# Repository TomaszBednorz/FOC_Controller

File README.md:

# FOC_Controller - in progress

## Description

The main goal of this project is to design a driver for a PMSM (Permanent Magnet Synchronous Motor) and implement the FOC (Field-Oriented Control) algorithm in software - in the future.

## Hardware overview

More information: [Hardware folder](https://github.com/TomaszBednorz/FOC_Controller/tree/main/HW)

## Figres

The FOC controller and PMSM motor.  

## STM32CubeIDE template

Empty project with pins and peripherals configuration: [Template](https://github.com/TomaszBednorz/FOC_Controller/tree/main/Tools/STM32CubeIDE_projects/STM32G473RC_template)

## Software overview

TBD

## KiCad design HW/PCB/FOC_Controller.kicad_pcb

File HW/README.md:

# FOC_Controller – Hardware

## Description

This folder contains:
- Source files of the PCB design in KiCad: [PCB folder](https://github.com/TomaszBednorz/FOC_Controller/tree/main/HW/PCB)
- STL files for the motor driver enclosure.

## 3D Visualization

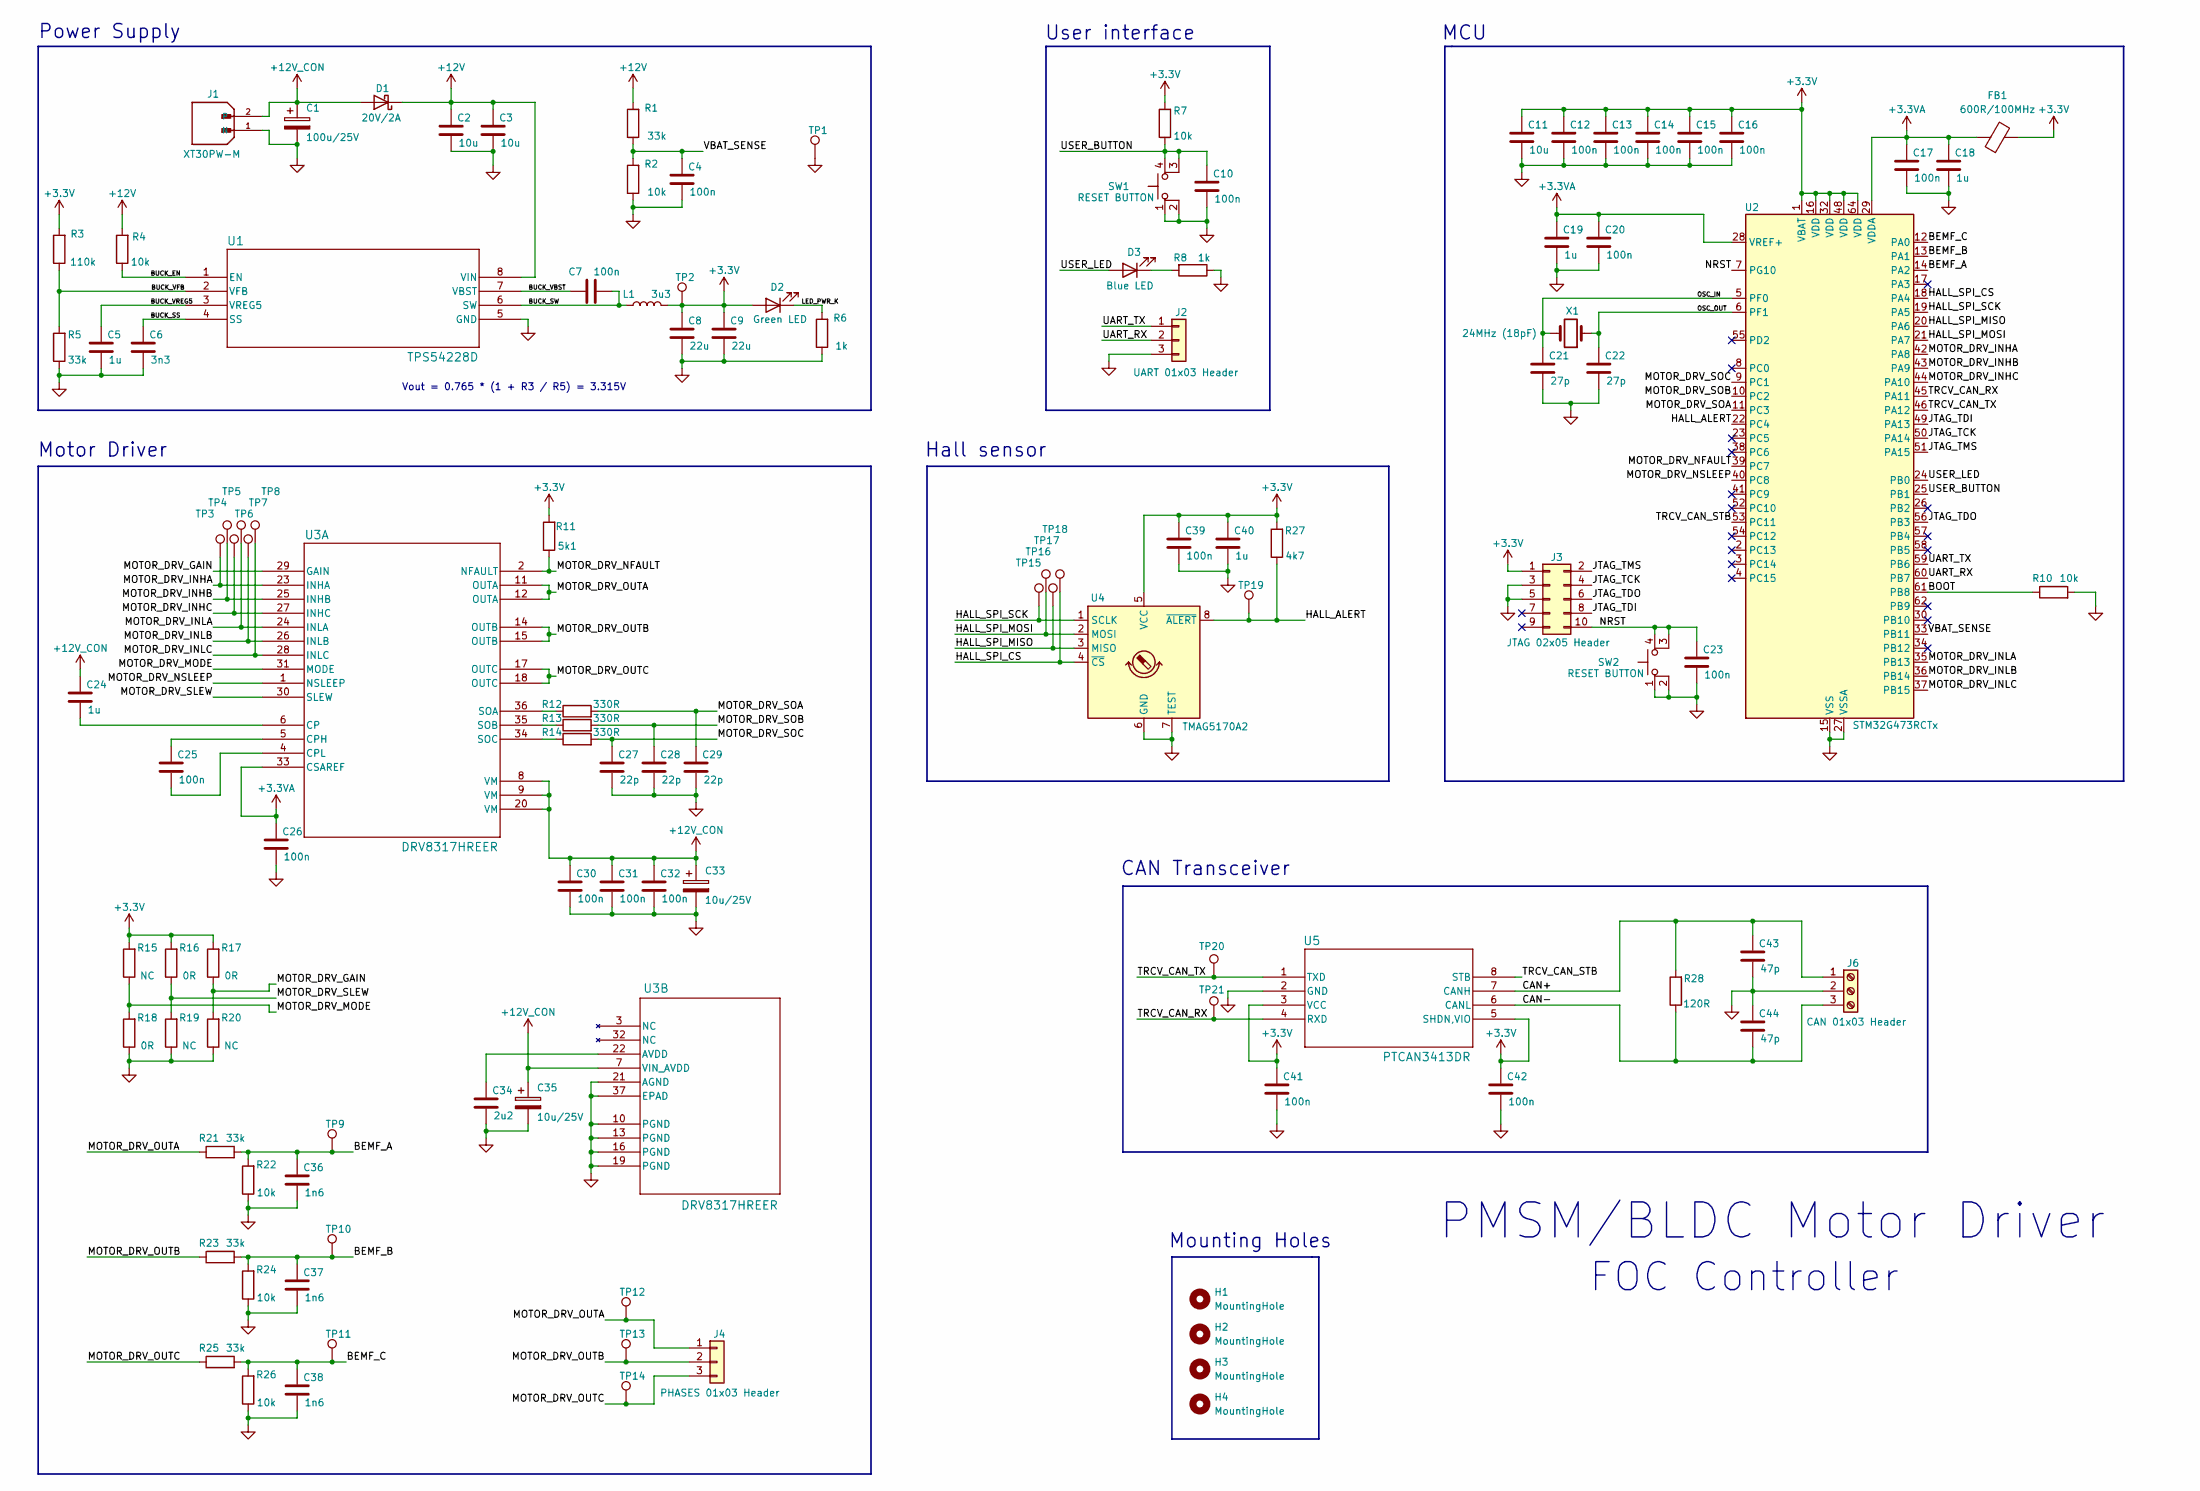
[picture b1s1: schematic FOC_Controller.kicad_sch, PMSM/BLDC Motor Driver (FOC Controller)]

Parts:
C1: 100u/25V; CP_Radial_D6.3mm_P2.50mm
C2, C3, C11: 10u; C_0805_2012Metric_Pad1.18x1.45mm_HandSolder
C4, C7, C10, C12, C13, C14, C15, C16, C17, C20, C23, C25, C26, C30, C31, C32, C39, C41, C42: 100n; C_0805_2012Metric_Pad1.18x1.45mm_HandSolder
C5, C18, C19, C24, C40: 1u; C_0805_2012Metric_Pad1.18x1.45mm_HandSolder
C6: 3n3; C_0805_2012Metric_Pad1.18x1.45mm_HandSolder
C8, C9: 22u; C_0805_2012Metric_Pad1.18x1.45mm_HandSolder
C21, C22: 27p; C_0603_1608Metric_Pad1.08x0.95mm_HandSolder
C27, C28, C29: 22p; C_0805_2012Metric_Pad1.18x1.45mm_HandSolder
C33, C35: 10u/25V; CP_Elec_4x3.9
C34: 2u2; C_0805_2012Metric_Pad1.18x1.45mm_HandSolder
C36, C37, C38: 1n6; C_0603_1608Metric_Pad1.08x0.95mm_HandSolder
C43, C44: 47p; C_0603_1608Metric_Pad1.08x0.95mm_HandSolder
D1: 20V/2A; D_SMB
D2: Green LED; LED_0805_2012Metric_Pad1.15x1.40mm_HandSolder
D3: Blue LED; LED_0805_2012Metric_Pad1.15x1.40mm_HandSolder
FB1: 600R/100MHz; L_0805_2012Metric_Pad1.05x1.20mm_HandSolder
H1, H2, H3, H4: MountingHole; MountingHole_2.2mm_M2
J1: XT30PW-M; AMASS_XT30PW-M_1x02_P2.50mm_Horizontal; PARTREV 1.2
J2: UART 01x03 Header; PinHeader_1x03_P2.54mm_Vertical
J3: JTAG 02x05 Header; PinHeader_2x05_P1.27mm_Vertical_SMD
J4: PHASES 01x03 Header; PinHeader_1x03_P2.54mm_Vertical
J6: CAN 01x03 Header; TerminalBlock_MetzConnect_Type059_RT06303HBWC_1x03_P3.50mm_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
L1: 3u3; L_APV_ANR4012
R1, R5, R21, R23, R25: 33k; R_0805_2012Metric_Pad1.20x1.40mm_HandSolder
R2, R4, R7, R10, R22, R24, R26: 10k; R_0805_2012Metric_Pad1.20x1.40mm_HandSolder
R3: 110k; R_0805_2012Metric_Pad1.20x1.40mm_HandSolder
R6, R8: 1k; R_0805_2012Metric_Pad1.20x1.40mm_HandSolder
R11: 5k1; R_0805_2012Metric_Pad1.20x1.40mm_HandSolder
R12, R13, R14: 330R; R_0805_2012Metric_Pad1.20x1.40mm_HandSolder
R15, R19, R20: NC; R_0805_2012Metric_Pad1.20x1.40mm_HandSolder
R16, R17, R18: 0R; R_0805_2012Metric_Pad1.20x1.40mm_HandSolder
R27: 4k7; R_0805_2012Metric_Pad1.20x1.40mm_HandSolder
R28: 120R; R_0805_2012Metric_Pad1.20x1.40mm_HandSolder
SW1, SW2: RESET BUTTON; SW_TS04-66-55-BK-100-SMT-TR
TP1, TP2, TP3, TP4, TP5, TP6, TP7, TP8, TP9, TP10, TP11, TP12, TP13, TP14, TP15, TP16, TP17, TP18, TP19, TP20, TP21: TestPoint; TestPoint_Pad_D1.0mm
U1: TPS54228D; SOIC-8_3.9x4.9mm_P1.27mm
U2: STM32G473RCTx; LQFP-64_10x10mm_P0.5mm
U3: DRV8317HREER; WQFN36_REE_TEX-L
U4: TMAG5170A2; VSSOP-8_3x3mm_P0.65mm
U5: PTCAN3413DR; SOIC-8_3.9x4.9mm_P1.27mm
X1: 24MHz (18pF); Crystal_SMD_Abracon_ABM3-2Pin_5.0x3.2mm_HandSoldering

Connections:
+3.3V: C8.1, C9.1, C11.1, C12.1, C13.1, C14.1, C15.1, C16.1, C39.1, C40.1, C41.1, C42.1, D2.2 (A), FB1.2, J3.1, L1.2, R3.2, R7.2, R11.2, R15.2, R16.2, R17.2, R27.2, TP2.1, U2.1 (VBAT), U2.16 (VDD), U2.32 (VDD), U2.48 (VDD), U2.64 (VDD), U4.5 (VCC), U5.3 (VCC), U5.5 (SHDN,VIO)
+3.3VA: C17.1, C18.1, C19.1, C20.1, C26.1, FB1.1, U2.28 (VREF+), U2.29 (VDDA), U3.33 (CSAREF)
+12V: C2.1, C3.1, D1.1 (K), R1.2, R4.2, U1.8 (VIN)
+12V_CON: C1.1, C24.1, C30.1, C31.1, C32.1, C33.1, C35.1, D1.2 (A), J1.2, U3.7 (VIN_AVDD), U3.8 (VM), U3.9 (VM), U3.20 (VM)
/BEMF_A: C36.1, R21.2, R22.2, TP9.1, U2.14 (PA2)
/BEMF_B: C37.1, R23.2, R24.2, TP10.1, U2.13 (PA1)
/BEMF_C: C38.1, R25.2, R26.2, TP11.1, U2.12 (PA0)
/BOOT: R10.1, U2.61 (PB8)
/BUCK_EN: R4.1, U1.1 (EN)
/BUCK_SS: C6.1, U1.4 (SS)
/BUCK_SW: C7.2, L1.1, U1.6 (SW)
/BUCK_VBST: C7.1, U1.7 (VBST)
/BUCK_VFB: R3.1, R5.2, U1.2 (VFB)
/BUCK_VREG5: C5.1, U1.3 (VREG5)
/CAN+: C43.1, J6.1, R28.2, U5.7 (CANH)
/CAN-: C44.2, J6.3, R28.1, U5.6 (CANL)
/HALL_ALERT: R27.1, TP19.1, U2.22 (PC4), U4.8 (~ALERT)
/HALL_SPI_CS: TP18.1, U2.18 (PA4), U4.4 (~CS)
/HALL_SPI_MISO: TP17.1, U2.20 (PA6), U4.3 (MISO)
/HALL_SPI_MOSI: TP16.1, U2.21 (PA7), U4.2 (MOSI)
/HALL_SPI_SCK: TP15.1, U2.19 (PA5), U4.1 (SCLK)
/JTAG_TCK: J3.4, U2.50 (PA14)
/JTAG_TDI: J3.8, U2.49 (PA13)
/JTAG_TDO: J3.6, U2.56 (PB3)
/JTAG_TMS: J3.2, U2.51 (PA15)
/LED_PWR_K: D2.1 (K), R6.2
/MOTOR_DRV_GAIN: R17.1, R20.2, U3.29 (GAIN)
/MOTOR_DRV_INHA: TP3.1, U2.42 (PA8), U3.23 (INHA)
/MOTOR_DRV_INHB: TP4.1, U2.43 (PA9), U3.25 (INHB)
/MOTOR_DRV_INHC: TP5.1, U2.44 (PA10), U3.27 (INHC)
/MOTOR_DRV_INLA: TP6.1, U2.35 (PB13), U3.24 (INLA)
/MOTOR_DRV_INLB: TP7.1, U2.36 (PB14), U3.26 (INLB)
/MOTOR_DRV_INLC: TP8.1, U2.37 (PB15), U3.28 (INLC)
/MOTOR_DRV_MODE: R15.1, R18.2, U3.31 (MODE)
/MOTOR_DRV_NFAULT: R11.1, U2.39 (PC7), U3.2 (NFAULT)
/MOTOR_DRV_NSLEEP: U2.40 (PC8), U3.1 (NSLEEP)
/MOTOR_DRV_OUTA: J4.1, R21.1, TP12.1, U3.11 (OUTA), U3.12 (OUTA)
/MOTOR_DRV_OUTB: J4.2, R23.1, TP13.1, U3.14 (OUTB), U3.15 (OUTB)
/MOTOR_DRV_OUTC: J4.3, R25.1, TP14.1, U3.17 (OUTC), U3.18 (OUTC)
/MOTOR_DRV_SLEW: R16.1, R19.2, U3.30 (SLEW)
/MOTOR_DRV_SOA: C29.1, R12.2, U2.11 (PC3)
/MOTOR_DRV_SOB: C28.1, R13.2, U2.10 (PC2)
/MOTOR_DRV_SOC: C27.1, R14.2, U2.9 (PC1)
/NRST: C23.1, J3.10, SW2.3 (K), SW2.4 (A), U2.7 (PG10)
/OSC_IN: C21.1, U2.5 (PF0), X1.2
/OSC_OUT: C22.1, U2.6 (PF1), X1.1
/TRCV_CAN_RX: TP21.1, U2.45 (PA11), U5.4 (RXD)
/TRCV_CAN_STB: U2.53 (PC11), U5.8 (STB)
/TRCV_CAN_TX: TP20.1, U2.46 (PA12), U5.1 (TXD)
/UART_RX: J2.2, U2.60 (PB7)
/UART_TX: J2.1, U2.59 (PB6)
/USER_BUTTON: C10.1, R7.1, SW1.3 (K), SW1.4 (A), U2.25 (PB1)
/USER_LED: D3.2 (A), U2.24 (PB0)
/VBAT_SENSE: C4.1, R1.1, R2.2, U2.33 (PB11)
GND: C1.2, C2.2, C3.2, C4.2, C5.2, C6.2, C8.2, C9.2, C10.2, C11.2, C12.2, C13.2, C14.2, C15.2, C16.2, C17.2, C18.2, C19.2, C20.2, C21.2, C22.2, C23.2, C26.2, C27.2, C28.2, C29.2, C30.2, C31.2, C32.2, C33.2, C34.2, C35.2, C36.2, C37.2, C38.2, C39.2, C40.2, C41.2, C42.2, C43.2, C44.1, J1.1 (N), J2.3, J3.3, J3.5, J6.2, R2.1, R5.1, R6.1, R8.1, R10.2, R18.1, R19.1, R20.1, R22.1, R24.1, R26.1, SW1.1, SW1.2, SW2.1, SW2.2, TP1.1, U1.5 (GND), U2.15 (VSS), U2.27 (VSSA), U2.31 (VSS), U2.47 (VSS), U2.63 (VSS), U3.10 (PGND), U3.13 (PGND), U3.16 (PGND), U3.19 (PGND), U3.21 (AGND), U3.37 (EPAD), U4.6 (GND), U4.7 (TEST), U5.2 (GND)
unnamed: D3.1 (K), R8.2
unnamed: C24.2, U3.6 (CP)
unnamed: C25.1, U3.5 (CPH)
unnamed: C25.2, U3.4 (CPL)
unnamed: R12.1, U3.36 (SOA)
unnamed: R13.1, U3.35 (SOB)
unnamed: R14.1, U3.34 (SOC)
unnamed: C34.1, U3.22 (AVDD)

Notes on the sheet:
Power Supply
User interface
Mounting Holes
Hall sensor
CAN Transceiver
MCU
Motor Driver
Vout = 0.765 * (1 + R3 / R5) = 3.315V
PMSM/BLDC Motor Driver
FOC Controller

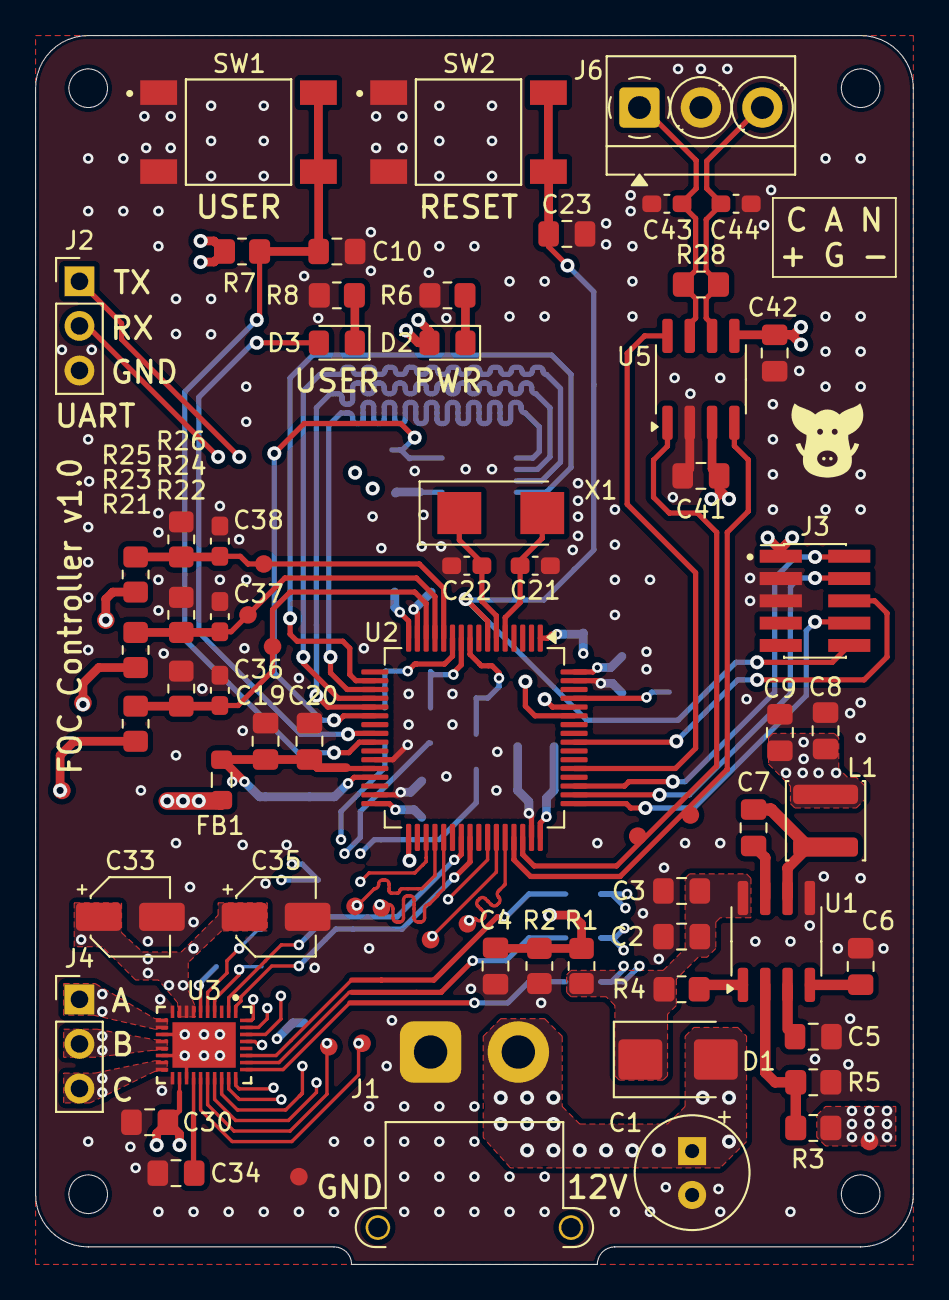
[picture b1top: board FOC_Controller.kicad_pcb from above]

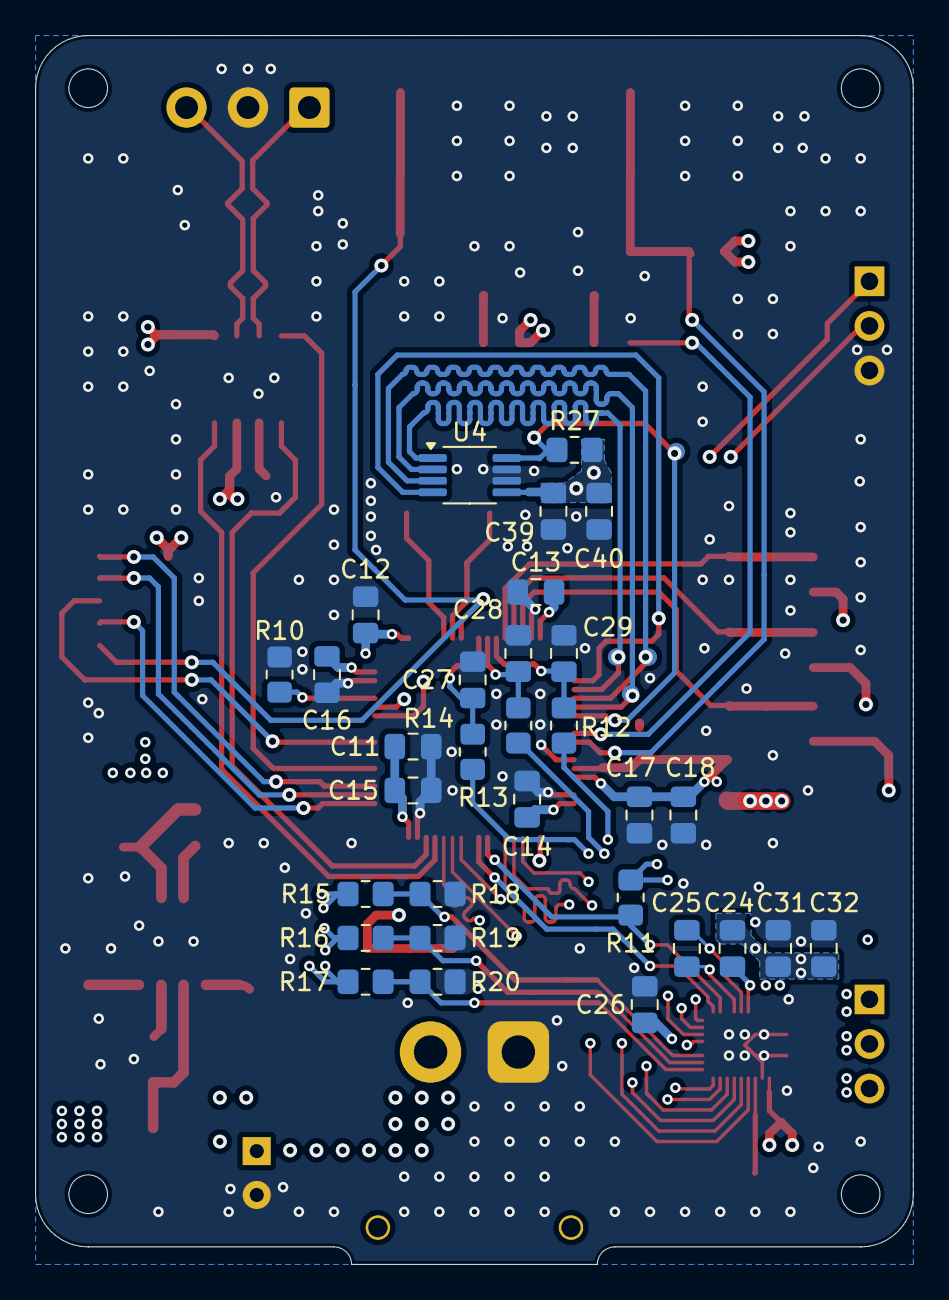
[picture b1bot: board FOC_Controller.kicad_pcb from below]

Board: 4 copper layers, 50.0 x 70.0 mm, 114 parts (36 on the bottom side), 63 nets.

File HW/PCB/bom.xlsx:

Component | Name | Price [zl] | Quantity | Sum | Status | Code case | Link | Designator
Integrated circuits
MCU | STM32G473RCT6 | 20.94 | 2 | 41.88 | Mouser |  | https://www.mouser.pl/ProductDetail/STMicroelectronics/STM32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 | U2
Motor driver | DRV8317HREER | 9.2899999999999991 | 2 | 18.579999999999998 | Mouser |  | https://www.mouser.pl/ProductDetail/Texas-Instruments/DRV831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 | U3
CAN-FD transceiver | TCAN3414DR | 5.81 | 2 | 11.62 | Mouser |  | https://www.mouser.pl/ProductDetail/Texas-Instruments/TCAN34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 | U5
Hall sensor | TMAG5170A2QDGKR | 7.1 | 2 | 14.2 | Mouser |  | https://www.mouser.pl/ProductDetail/Texas-Instruments/TMAG51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 | U4
Step-down converter | TPS54228D | 4.6900000000000004 | 2 | 9.3800000000000008 | Mouser |  | https://www.mouser.pl/ProductDetail/Texas-Instruments/TPS542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 | U1
Resistors
33k | CRCW080533K0FKEBC | 6.5000000000000002E-2 | 15 | 0.97500000000000009 | Mouser | 0805 | https://www.mouser.pl/ProductDetail/Vishay-Dale/CRCW080533K0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 | R1, R5, R21, R23, R25
10k | CRCW080510K0FKEA | 0.17199999999999999 | 21 | 3.6119999999999997 | Mouser | 0805 | https://www.mouser.pl/ProductDetail/Vishay-Dale/CRCW080510K0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 | R2, R4, R7, R10, R22, R24, R26
110k | CRCW0805110KFKEAC | 9.9000000000000005E-2 | 10 | 0.99 | Mouser | 0805 | https://www.mouser.pl/ProductDetail/Vishay-Dale/CRCW0805110K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 | R3
1k | CRCW08051K00FKEAC | 9.9000000000000005E-2 | 10 | 0.99 | Mouser | 0805 | https://www.mouser.pl/ProductDetail/Vishay-Dale/CRCW08051K00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 | R6,R8
0R | AC0805FR-070RL | 6.5000000000000002E-2 | 10 | 0.65 | Mouser | 0805 | https://www.mouser.pl/ProductDetail/YAGEO/AC0805FR-070RL?qs=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 | R9 (brak), R16, R17, R19
5k1 | CRCW08055K10FKEAC | 9.9000000000000005E-2 | 10 | 0.99 | Mouser | 0805 | https://www.mouser.pl/ProductDetail/Vishay-Dale/CRCW08055K10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 | R11
330R | CRCW0805330RFKEA | 0.10299999999999999 | 10 | 1.03 | Mouser | 0805 | https://www.mouser.pl/ProductDetail/Vishay-Dale/CRCW0805330R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 | R12, R13, R14 |  |  |  |  |  |  |  |  |  |  |  |  |  |  | -
4k7 | CRCW08054K70FKEA | 0.12 | 10 | 1.2 | Mouser | 0805 | https://www.mouser.pl/ProductDetail/Vishay-Dale/CRCW08054K70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 | R27
120R | CRCW0805120RFKEA | 0.159 | 10 | 1.59 | Mouser | 0805 | https://www.mouser.pl/ProductDetail/Vishay-Dale/CRCW0805120R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 | R28
NC |  |  | 9 | 0 |  |  |  | R15, R19, R20
Capacitors
100u/25V, electrolytic | 860010473007 | 0.53 | 2 | 1.06 | Mouser | THT | https://www.mouser.pl/ProductDetail/Wurth-Elektronik/8600104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 | C1
10u/25V | CL21A106KAYNNNG | 0.30099999999999999 | 10 | 3.01 | Mouser | 0805 | https://www.mouser.pl/ProductDetail/Samsung-Electro-Mechanic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 | C2, C3, C11
100n/50V | CL21B104KBCNNND | 7.6999999999999999E-2 | 100 | 7.7 | Mouser | 0805 | https://www.mouser.pl/ProductDetail/Samsung-Electro-Mechanic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 | C4, C7, C10, C12, C13, C14, C15, C16, C17, C20, C23, C25, C26, C30, C31, C32, C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
1u/50V | CL21B105KBFNNNE | 0.151 | 15 | 2.2650000000000001 | Mouser | 0805 | https://www.mouser.pl/ProductDetail/Samsung-Electro-Mechanic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 | C5, C18, C19, C24, C40
3n3/25V | 885012207063 | 0.155 | 10 | 1.55 | Mouser | 0805 | https://www.mouser.pl/ProductDetail/Wurth-Elektronik/8850122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 | C6
22u/25V | CL21A226MAYNNNE | 0.42599999999999999 | 15 | 6.39 | Mouser | 0805 | https://www.mouser.pl/ProductDetail/Samsung-Electro-Mechanic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 | C8, C9, C27, C28, C29
27p/50V | CL10C270JB81PNC | 0.11600000000000001 | 10 | 1.1600000000000001 | Mouser | 0603 | https://www.mouser.pl/ProductDetail/Samsung-Electro-Mechanic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 | C21, C22
10u/25V, electrolytic | 865080440002 | 0.74 | 4 | 2.96 | Mouser | SMD | https://www.mouser.pl/ProductDetail/Wurth-Elektronik/8650804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 | C33, C35
2u2/25V | CL21A225KAFNNNG | 0.219 | 10 | 2.19 | Mouser | 0805 | https://www.mouser.pl/ProductDetail/Samsung-Electro-Mechanic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 | C34
1n6/50V | GRM1885C1H162JA01D | 0.129 | 10 | 1.29 | TME | 0603 | https://www.tme.eu/pl/details/grm1885c1h162ja01d/kondensator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 | C36, C37, C38
47p | CL10C470JC81PNC | 0.16300000000000001 | 10 | 1.6300000000000001 | Mouser | 0603 | https://www.mouser.pl/ProductDetail/Samsung-Electro-Mechanic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 | C43, C44
Inductors
3u3 | NRS4012T3R3MDGJ | 0.78 | 3 | 2.34 | Mouser |  | https://www.mouser.pl/ProductDetail/TAIYO-YUDEN/NRS4012T3R3M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 | L1
Diodes
Schottky Diodes | SK22 | 0.74 | 3 | 2.2199999999999998 | Mouser |  | https://www.mouser.pl/ProductDetail/Diotec-Semiconductor/SK2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 | D1
LED green | 150080GS75000 | 0.78 | 3 | 2.34 | Mouser |  | https://www.mouser.pl/ProductDetail/Wurth-Elektronik/150080G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 | D2
LED blue | 150080BS75000 | 0.78 | 3 | 2.34 | Mouser |  | https://www.mouser.pl/ProductDetail/Wurth-Elektronik/150080B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 | D3
Ferrite Beads
600R/100Mhz | MPZ2012S601ATD25 | 0.28000000000000003 | 10 | 2.8000000000000003 | Mouser | 0805 | https://www.mouser.pl/ProductDetail/TDK/MPZ2012S601ATD25?qs=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 | FB1
Cristals
24MHz | ABM3-24.000MHZ-D2Y-T | 2.21 | 2 | 4.42 | Mouser |  | https://www.mouser.pl/ProductDetail/ABRACON/ABM3-24.000MHZ-D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 | X1
Switches
Tactile Switch | TS04-66-55-BK-100-SMT | 0.66 | 4 | 2.64 | Mouser |  | https://www.mouser.pl/ProductDetail/Same-Sky/TS04-66-55-BK-1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 | SW1, SW2
Connectors
DC male connector | XT30PW-M | 2.54 | 2 | 5.08 | TME |  | https://www.tme.eu/pl/details/xt30pw-m/zlacza-dc/amass/ | J1
DC female connector | XT30U-F | 1.75 | 2 | 3.5 | TME |  | https://www.tme.eu/pl/details/xt30u-f/zlacza-dc/amass/ | J1
Header 1x10 (goldpin) | 10129378-910001BLF | 0.78 | 2 | 1.56 | Mouser |  | https://www.mouser.pl/ProductDetail/Amphenol-FCI/10129378-91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 | J2, J4
Header 2x5 | 20021121-00010T4LF | 3.23 | 2 | 6.46 | Mouser |  | https://www.mouser.pl/ProductDetail/Amphenol-FCI/20021121-00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 | J3
Screw terminal 1x3 | EBWA-03-A | 1.76 | 2 | 3.52 | Mouser |  | https://www.mouser.pl/ProductDetail/Adam-Tech/EBWA-03-A?qs=H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 | J6
Jumper 1x2 | MSA-G | 0.41 | 3 | 1.23 | Mouser |  | https://www.mouser.pl/ProductDetail/Adam-Tech/MSA-G?qs=TTVbH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 | J5
 |  |  | Łącznie | 179.34199999999998

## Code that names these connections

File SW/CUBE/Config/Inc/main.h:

/* USER CODE BEGIN Header */
/**
  ******************************************************************************
  * @file           : main.h
  * @brief          : Header for main.c file.
  *                   This file contains the common defines of the application.
  ******************************************************************************
  * @attention
  *
  * Copyright (c) 2025 STMicroelectronics.
  * All rights reserved.
  *
  * This software is licensed under terms that can be found in the LICENSE file
  * in the root directory of this software component.
  * If no LICENSE file comes with this software, it is provided AS-IS.
  *
  ******************************************************************************
  */
/* USER CODE END Header */

/* Define to prevent recursive inclusion -------------------------------------*/
#ifndef __MAIN_H
#define __MAIN_H

#ifdef __cplusplus
extern "C" {
#endif

/* Includes ------------------------------------------------------------------*/
#include "stm32g4xx_hal.h"

/* Private includes ----------------------------------------------------------*/
/* USER CODE BEGIN Includes */

/* USER CODE END Includes */

/* Exported types ------------------------------------------------------------*/
/* USER CODE BEGIN ET */

/* USER CODE END ET */

/* Exported constants --------------------------------------------------------*/
/* USER CODE BEGIN EC */

/* USER CODE END EC */

/* Exported macro ------------------------------------------------------------*/
/* USER CODE BEGIN EM */

/* USER CODE END EM */

/* Exported functions prototypes ---------------------------------------------*/
void Error_Handler(void);

/* USER CODE BEGIN EFP */

/* USER CODE END EFP */

/* Private defines -----------------------------------------------------------*/
#define DEBUG_PIN_RED_Pin GPIO_PIN_13
#define DEBUG_PIN_RED_GPIO_Port GPIOC
#define DEBUG_PIN_BLUE_Pin GPIO_PIN_15
#define DEBUG_PIN_BLUE_GPIO_Port GPIOC
#define NRST_Pin GPIO_PIN_10
#define NRST_GPIO_Port GPIOG
#define MOTOR_DRV_SOC_Pin GPIO_PIN_1
#define MOTOR_DRV_SOC_GPIO_Port GPIOC
#define MOTOR_DRV_SOB_Pin GPIO_PIN_2
#define MOTOR_DRV_SOB_GPIO_Port GPIOC
#define MOTOR_DRV_SOA_Pin GPIO_PIN_3
#define MOTOR_DRV_SOA_GPIO_Port GPIOC
#define BEMF_C_Pin GPIO_PIN_0
#define BEMF_C_GPIO_Port GPIOA
#define BEMF_B_Pin GPIO_PIN_1
#define BEMF_B_GPIO_Port GPIOA
#define BEMF_A_Pin GPIO_PIN_2
#define BEMF_A_GPIO_Port GPIOA
#define HALL_SPI_CS_Pin GPIO_PIN_4
#define HALL_SPI_CS_GPIO_Port GPIOA
#define HALL_SPI_SCK_Pin GPIO_PIN_5
#define HALL_SPI_SCK_GPIO_Port GPIOA
#define HALL_SPI_MISO_Pin GPIO_PIN_6
#define HALL_SPI_MISO_GPIO_Port GPIOA
#define HALL_SPI_MOSI_Pin GPIO_PIN_7
#define HALL_SPI_MOSI_GPIO_Port GPIOA
#define HALL_ALERT_Pin GPIO_PIN_4
#define HALL_ALERT_GPIO_Port GPIOC
#define USER_LED_Pin GPIO_PIN_0
#define USER_LED_GPIO_Port GPIOB
#define USER_BUTTON_Pin GPIO_PIN_1
#define USER_BUTTON_GPIO_Port GPIOB
#define VBAT_SENSE_Pin GPIO_PIN_11
#define VBAT_SENSE_GPIO_Port GPIOB
#define MOTOR_DRV_INLA_Pin GPIO_PIN_13
#define MOTOR_DRV_INLA_GPIO_Port GPIOB
#define MOTOR_DRV_INLB_Pin GPIO_PIN_14
#define MOTOR_DRV_INLB_GPIO_Port GPIOB
#define MOTOR_DRV_INLC_Pin GPIO_PIN_15
#define MOTOR_DRV_INLC_GPIO_Port GPIOB
#define MOTOR_DRV_NFAULT_Pin GPIO_PIN_7
#define MOTOR_DRV_NFAULT_GPIO_Port GPIOC
#define MOTOR_DRV_NSLEEP_Pin GPIO_PIN_8
#define MOTOR_DRV_NSLEEP_GPIO_Port GPIOC
#define MOTOR_DRV_INHA_Pin GPIO_PIN_8
#define MOTOR_DRV_INHA_GPIO_Port GPIOA
#define MOTOR_DRV_INHB_Pin GPIO_PIN_9
#define MOTOR_DRV_INHB_GPIO_Port GPIOA
#define MOTOR_DRV_INHC_Pin GPIO_PIN_10
#define MOTOR_DRV_INHC_GPIO_Port GPIOA
#define CAN_TRCV_STB_Pin GPIO_PIN_11
#define CAN_TRCV_STB_GPIO_Port GPIOC
#define UART_TX_Pin GPIO_PIN_6
#define UART_TX_GPIO_Port GPIOB
#define UART_RX_Pin GPIO_PIN_7
#define UART_RX_GPIO_Port GPIOB
#define BOOT_Pin GPIO_PIN_8
#define BOOT_GPIO_Port GPIOB

/* USER CODE BEGIN Private defines */

/* USER CODE END Private defines */

#ifdef __cplusplus
}
#endif

#endif /* __MAIN_H */

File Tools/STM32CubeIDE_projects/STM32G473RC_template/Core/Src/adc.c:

/* USER CODE BEGIN Header */
/**
  ******************************************************************************
  * @file    adc.c
  * @brief   This file provides code for the configuration
  *          of the ADC instances.
  ******************************************************************************
  * @attention
  *
  * Copyright (c) 2025 STMicroelectronics.
  * All rights reserved.
  *
  * This software is licensed under terms that can be found in the LICENSE file
  * in the root directory of this software component.
  * If no LICENSE file comes with this software, it is provided AS-IS.
  *
  ******************************************************************************
  */
/* USER CODE END Header */
/* Includes ------------------------------------------------------------------*/
#include "adc.h"

/* USER CODE BEGIN 0 */

/* USER CODE END 0 */

ADC_HandleTypeDef hadc1;

/* ADC1 init function */
void MX_ADC1_Init(void)
{

  /* USER CODE BEGIN ADC1_Init 0 */

  /* USER CODE END ADC1_Init 0 */

  ADC_MultiModeTypeDef multimode = {0};
  ADC_ChannelConfTypeDef sConfig = {0};

  /* USER CODE BEGIN ADC1_Init 1 */

  /* USER CODE END ADC1_Init 1 */

  /** Common config
  */
  hadc1.Instance = ADC1;
  hadc1.Init.ClockPrescaler = ADC_CLOCK_SYNC_PCLK_DIV4;
  hadc1.Init.Resolution = ADC_RESOLUTION_12B;
  hadc1.Init.DataAlign = ADC_DATAALIGN_RIGHT;
  hadc1.Init.GainCompensation = 0;
  hadc1.Init.ScanConvMode = ADC_SCAN_DISABLE;
  hadc1.Init.EOCSelection = ADC_EOC_SINGLE_CONV;
  hadc1.Init.LowPowerAutoWait = DISABLE;
  hadc1.Init.ContinuousConvMode = DISABLE;
  hadc1.Init.NbrOfConversion = 1;
  hadc1.Init.DiscontinuousConvMode = DISABLE;
  hadc1.Init.ExternalTrigConv = ADC_SOFTWARE_START;
  hadc1.Init.ExternalTrigConvEdge = ADC_EXTERNALTRIGCONVEDGE_NONE;
  hadc1.Init.DMAContinuousRequests = DISABLE;
  hadc1.Init.Overrun = ADC_OVR_DATA_PRESERVED;
  hadc1.Init.OversamplingMode = DISABLE;
  if (HAL_ADC_Init(&hadc1) != HAL_OK)
  {
    Error_Handler();
  }

  /** Configure the ADC multi-mode
  */
  multimode.Mode = ADC_MODE_INDEPENDENT;
  if (HAL_ADCEx_MultiModeConfigChannel(&hadc1, &multimode) != HAL_OK)
  {
    Error_Handler();
  }

  /** Configure Regular Channel
  */
  sConfig.Channel = ADC_CHANNEL_7;
  sConfig.Rank = ADC_REGULAR_RANK_1;
  sConfig.SamplingTime = ADC_SAMPLETIME_2CYCLES_5;
  sConfig.SingleDiff = ADC_SINGLE_ENDED;
  sConfig.OffsetNumber = ADC_OFFSET_NONE;
  sConfig.Offset = 0;
  if (HAL_ADC_ConfigChannel(&hadc1, &sConfig) != HAL_OK)
  {
    Error_Handler();
  }
  /* USER CODE BEGIN ADC1_Init 2 */

  /* USER CODE END ADC1_Init 2 */

}

void HAL_ADC_MspInit(ADC_HandleTypeDef* adcHandle)
{

  GPIO_InitTypeDef GPIO_InitStruct = {0};
  RCC_PeriphCLKInitTypeDef PeriphClkInit = {0};
  if(adcHandle->Instance==ADC1)
  {
  /* USER CODE BEGIN ADC1_MspInit 0 */

  /* USER CODE END ADC1_MspInit 0 */

  /** Initializes the peripherals clocks
  */
    PeriphClkInit.PeriphClockSelection = RCC_PERIPHCLK_ADC12;
    PeriphClkInit.Adc12ClockSelection = RCC_ADC12CLKSOURCE_SYSCLK;
    if (HAL_RCCEx_PeriphCLKConfig(&PeriphClkInit) != HAL_OK)
    {
      Error_Handler();
    }

    /* ADC1 clock enable */
    __HAL_RCC_ADC12_CLK_ENABLE();

    __HAL_RCC_GPIOC_CLK_ENABLE();
    __HAL_RCC_GPIOA_CLK_ENABLE();
    __HAL_RCC_GPIOB_CLK_ENABLE();
    /**ADC1 GPIO Configuration
    PC1     ------> ADC1_IN7
    PC2     ------> ADC1_IN8
    PC3     ------> ADC1_IN9
    PA0     ------> ADC1_IN1
    PA1     ------> ADC1_IN2
    PA2     ------> ADC1_IN3
    PB11     ------> ADC1_IN14
    */
    GPIO_InitStruct.Pin = MOTOR_DRV_SOC_Pin|MOTOR_DRV_SOB_Pin|MOTOR_DRV_SOA_Pin;
    GPIO_InitStruct.Mode = GPIO_MODE_ANALOG;
    GPIO_InitStruct.Pull = GPIO_NOPULL;
    HAL_GPIO_Init(GPIOC, &GPIO_InitStruct);

    GPIO_InitStruct.Pin = BEMF_C_Pin|BEMF_B_Pin|BEMF_A_Pin;
    GPIO_InitStruct.Mode = GPIO_MODE_ANALOG;
    GPIO_InitStruct.Pull = GPIO_NOPULL;
    HAL_GPIO_Init(GPIOA, &GPIO_InitStruct);

    GPIO_InitStruct.Pin = VBAT_SENSE_Pin;
    GPIO_InitStruct.Mode = GPIO_MODE_ANALOG;
    GPIO_InitStruct.Pull = GPIO_NOPULL;
    HAL_GPIO_Init(VBAT_SENSE_GPIO_Port, &GPIO_InitStruct);

  /* USER CODE BEGIN ADC1_MspInit 1 */

  /* USER CODE END ADC1_MspInit 1 */
  }
}

void HAL_ADC_MspDeInit(ADC_HandleTypeDef* adcHandle)
{

  if(adcHandle->Instance==ADC1)
  {
  /* USER CODE BEGIN ADC1_MspDeInit 0 */

  /* USER CODE END ADC1_MspDeInit 0 */
    /* Peripheral clock disable */
    __HAL_RCC_ADC12_CLK_DISABLE();

    /**ADC1 GPIO Configuration
    PC1     ------> ADC1_IN7
    PC2     ------> ADC1_IN8
    PC3     ------> ADC1_IN9
    PA0     ------> ADC1_IN1
    PA1     ------> ADC1_IN2
    PA2     ------> ADC1_IN3
    PB11     ------> ADC1_IN14
    */
    HAL_GPIO_DeInit(GPIOC, MOTOR_DRV_SOC_Pin|MOTOR_DRV_SOB_Pin|MOTOR_DRV_SOA_Pin);

    HAL_GPIO_DeInit(GPIOA, BEMF_C_Pin|BEMF_B_Pin|BEMF_A_Pin);

    HAL_GPIO_DeInit(VBAT_SENSE_GPIO_Port, VBAT_SENSE_Pin);

  /* USER CODE BEGIN ADC1_MspDeInit 1 */

  /* USER CODE END ADC1_MspDeInit 1 */
  }
}

/* USER CODE BEGIN 1 */

/* USER CODE END 1 */

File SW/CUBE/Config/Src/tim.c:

/* USER CODE BEGIN Header */
/**
  ******************************************************************************
  * @file    tim.c
  * @brief   This file provides code for the configuration
  *          of the TIM instances.
  ******************************************************************************
  * @attention
  *
  * Copyright (c) 2025 STMicroelectronics.
  * All rights reserved.
  *
  * This software is licensed under terms that can be found in the LICENSE file
  * in the root directory of this software component.
  * If no LICENSE file comes with this software, it is provided AS-IS.
  *
  ******************************************************************************
  */
/* USER CODE END Header */
/* Includes ------------------------------------------------------------------*/
#include "tim.h"

/* USER CODE BEGIN 0 */

/* USER CODE END 0 */

TIM_HandleTypeDef htim1;

/* TIM1 init function */
void MX_TIM1_Init(void)
{

  /* USER CODE BEGIN TIM1_Init 0 */

  /* USER CODE END TIM1_Init 0 */

  TIM_ClockConfigTypeDef sClockSourceConfig = {0};
  TIM_MasterConfigTypeDef sMasterConfig = {0};
  TIM_OC_InitTypeDef sConfigOC = {0};
  TIM_BreakDeadTimeConfigTypeDef sBreakDeadTimeConfig = {0};

  /* USER CODE BEGIN TIM1_Init 1 */

  /* USER CODE END TIM1_Init 1 */
  htim1.Instance = TIM1;
  htim1.Init.Prescaler = 159;
  htim1.Init.CounterMode = TIM_COUNTERMODE_CENTERALIGNED1;
  htim1.Init.Period = 99;
  htim1.Init.ClockDivision = TIM_CLOCKDIVISION_DIV1;
  htim1.Init.RepetitionCounter = 0;
  htim1.Init.AutoReloadPreload = TIM_AUTORELOAD_PRELOAD_ENABLE;
  if (HAL_TIM_Base_Init(&htim1) != HAL_OK)
  {
    Error_Handler();
  }
  sClockSourceConfig.ClockSource = TIM_CLOCKSOURCE_INTERNAL;
  if (HAL_TIM_ConfigClockSource(&htim1, &sClockSourceConfig) != HAL_OK)
  {
    Error_Handler();
  }
  if (HAL_TIM_PWM_Init(&htim1) != HAL_OK)
  {
    Error_Handler();
  }
  sMasterConfig.MasterOutputTrigger = TIM_TRGO_RESET;
  sMasterConfig.MasterOutputTrigger2 = TIM_TRGO2_RESET;
  sMasterConfig.MasterSlaveMode = TIM_MASTERSLAVEMODE_DISABLE;
  if (HAL_TIMEx_MasterConfigSynchronization(&htim1, &sMasterConfig) != HAL_OK)
  {
    Error_Handler();
  }
  sConfigOC.OCMode = TIM_OCMODE_PWM1;
  sConfigOC.Pulse = 0;
  sConfigOC.OCPolarity = TIM_OCPOLARITY_HIGH;
  sConfigOC.OCNPolarity = TIM_OCNPOLARITY_HIGH;
  sConfigOC.OCFastMode = TIM_OCFAST_DISABLE;
  sConfigOC.OCIdleState = TIM_OCIDLESTATE_RESET;
  sConfigOC.OCNIdleState = TIM_OCNIDLESTATE_RESET;
  if (HAL_TIM_PWM_ConfigChannel(&htim1, &sConfigOC, TIM_CHANNEL_1) != HAL_OK)
  {
    Error_Handler();
  }
  if (HAL_TIM_PWM_ConfigChannel(&htim1, &sConfigOC, TIM_CHANNEL_2) != HAL_OK)
  {
    Error_Handler();
  }
  if (HAL_TIM_PWM_ConfigChannel(&htim1, &sConfigOC, TIM_CHANNEL_3) != HAL_OK)
  {
    Error_Handler();
  }
  sBreakDeadTimeConfig.OffStateRunMode = TIM_OSSR_DISABLE;
  sBreakDeadTimeConfig.OffStateIDLEMode = TIM_OSSI_DISABLE;
  sBreakDeadTimeConfig.LockLevel = TIM_LOCKLEVEL_OFF;
  sBreakDeadTimeConfig.DeadTime = 0;
  sBreakDeadTimeConfig.BreakState = TIM_BREAK_DISABLE;
  sBreakDeadTimeConfig.BreakPolarity = TIM_BREAKPOLARITY_HIGH;
  sBreakDeadTimeConfig.BreakFilter = 0;
  sBreakDeadTimeConfig.BreakAFMode = TIM_BREAK_AFMODE_INPUT;
  sBreakDeadTimeConfig.Break2State = TIM_BREAK2_DISABLE;
  sBreakDeadTimeConfig.Break2Polarity = TIM_BREAK2POLARITY_HIGH;
  sBreakDeadTimeConfig.Break2Filter = 0;
  sBreakDeadTimeConfig.Break2AFMode = TIM_BREAK_AFMODE_INPUT;
  sBreakDeadTimeConfig.AutomaticOutput = TIM_AUTOMATICOUTPUT_DISABLE;
  if (HAL_TIMEx_ConfigBreakDeadTime(&htim1, &sBreakDeadTimeConfig) != HAL_OK)
  {
    Error_Handler();
  }
  /* USER CODE BEGIN TIM1_Init 2 */

  /* USER CODE END TIM1_Init 2 */
  HAL_TIM_MspPostInit(&htim1);

}

void HAL_TIM_Base_MspInit(TIM_HandleTypeDef* tim_baseHandle)
{

  if(tim_baseHandle->Instance==TIM1)
  {
  /* USER CODE BEGIN TIM1_MspInit 0 */

  /* USER CODE END TIM1_MspInit 0 */
    /* TIM1 clock enable */
    __HAL_RCC_TIM1_CLK_ENABLE();
  /* USER CODE BEGIN TIM1_MspInit 1 */

  /* USER CODE END TIM1_MspInit 1 */
  }
}
void HAL_TIM_MspPostInit(TIM_HandleTypeDef* timHandle)
{

  GPIO_InitTypeDef GPIO_InitStruct = {0};
  if(timHandle->Instance==TIM1)
  {
  /* USER CODE BEGIN TIM1_MspPostInit 0 */

  /* USER CODE END TIM1_MspPostInit 0 */

    __HAL_RCC_GPIOB_CLK_ENABLE();
    __HAL_RCC_GPIOA_CLK_ENABLE();
    /**TIM1 GPIO Configuration
    PB13     ------> TIM1_CH1N
    PB14     ------> TIM1_CH2N
    PB15     ------> TIM1_CH3N
    PA8     ------> TIM1_CH1
    PA9     ------> TIM1_CH2
    PA10     ------> TIM1_CH3
    */
    GPIO_InitStruct.Pin = MOTOR_DRV_INLA_Pin|MOTOR_DRV_INLB_Pin;
    GPIO_InitStruct.Mode = GPIO_MODE_AF_PP;
    GPIO_InitStruct.Pull = GPIO_NOPULL;
    GPIO_InitStruct.Speed = GPIO_SPEED_FREQ_LOW;
    GPIO_InitStruct.Alternate = GPIO_AF6_TIM1;
    HAL_GPIO_Init(GPIOB, &GPIO_InitStruct);

    GPIO_InitStruct.Pin = MOTOR_DRV_INLC_Pin;
    GPIO_InitStruct.Mode = GPIO_MODE_AF_PP;
    GPIO_InitStruct.Pull = GPIO_NOPULL;
    GPIO_InitStruct.Speed = GPIO_SPEED_FREQ_LOW;
    GPIO_InitStruct.Alternate = GPIO_AF4_TIM1;
    HAL_GPIO_Init(MOTOR_DRV_INLC_GPIO_Port, &GPIO_InitStruct);

    GPIO_InitStruct.Pin = MOTOR_DRV_INHA_Pin|MOTOR_DRV_INHB_Pin|MOTOR_DRV_INHC_Pin;
    GPIO_InitStruct.Mode = GPIO_MODE_AF_PP;
    GPIO_InitStruct.Pull = GPIO_NOPULL;
    GPIO_InitStruct.Speed = GPIO_SPEED_FREQ_LOW;
    GPIO_InitStruct.Alternate = GPIO_AF6_TIM1;
    HAL_GPIO_Init(GPIOA, &GPIO_InitStruct);

  /* USER CODE BEGIN TIM1_MspPostInit 1 */

  /* USER CODE END TIM1_MspPostInit 1 */
  }

}

void HAL_TIM_Base_MspDeInit(TIM_HandleTypeDef* tim_baseHandle)
{

  if(tim_baseHandle->Instance==TIM1)
  {
  /* USER CODE BEGIN TIM1_MspDeInit 0 */

  /* USER CODE END TIM1_MspDeInit 0 */
    /* Peripheral clock disable */
    __HAL_RCC_TIM1_CLK_DISABLE();
  /* USER CODE BEGIN TIM1_MspDeInit 1 */

  /* USER CODE END TIM1_MspDeInit 1 */
  }
}

/* USER CODE BEGIN 1 */

/* USER CODE END 1 */

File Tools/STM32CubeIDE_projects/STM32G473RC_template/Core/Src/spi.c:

/* USER CODE BEGIN Header */
/**
  ******************************************************************************
  * @file    spi.c
  * @brief   This file provides code for the configuration
  *          of the SPI instances.
  ******************************************************************************
  * @attention
  *
  * Copyright (c) 2025 STMicroelectronics.
  * All rights reserved.
  *
  * This software is licensed under terms that can be found in the LICENSE file
  * in the root directory of this software component.
  * If no LICENSE file comes with this software, it is provided AS-IS.
  *
  ******************************************************************************
  */
/* USER CODE END Header */
/* Includes ------------------------------------------------------------------*/
#include "spi.h"

/* USER CODE BEGIN 0 */

/* USER CODE END 0 */

SPI_HandleTypeDef hspi1;

/* SPI1 init function */
void MX_SPI1_Init(void)
{

  /* USER CODE BEGIN SPI1_Init 0 */

  /* USER CODE END SPI1_Init 0 */

  /* USER CODE BEGIN SPI1_Init 1 */

  /* USER CODE END SPI1_Init 1 */
  hspi1.Instance = SPI1;
  hspi1.Init.Mode = SPI_MODE_MASTER;
  hspi1.Init.Direction = SPI_DIRECTION_2LINES;
  hspi1.Init.DataSize = SPI_DATASIZE_8BIT;
  hspi1.Init.CLKPolarity = SPI_POLARITY_LOW;
  hspi1.Init.CLKPhase = SPI_PHASE_1EDGE;
  hspi1.Init.NSS = SPI_NSS_SOFT;
  hspi1.Init.BaudRatePrescaler = SPI_BAUDRATEPRESCALER_16;
  hspi1.Init.FirstBit = SPI_FIRSTBIT_MSB;
  hspi1.Init.TIMode = SPI_TIMODE_DISABLE;
  hspi1.Init.CRCCalculation = SPI_CRCCALCULATION_DISABLE;
  hspi1.Init.CRCPolynomial = 7;
  hspi1.Init.CRCLength = SPI_CRC_LENGTH_DATASIZE;
  hspi1.Init.NSSPMode = SPI_NSS_PULSE_ENABLE;
  if (HAL_SPI_Init(&hspi1) != HAL_OK)
  {
    Error_Handler();
  }
  /* USER CODE BEGIN SPI1_Init 2 */

  /* USER CODE END SPI1_Init 2 */

}

void HAL_SPI_MspInit(SPI_HandleTypeDef* spiHandle)
{

  GPIO_InitTypeDef GPIO_InitStruct = {0};
  if(spiHandle->Instance==SPI1)
  {
  /* USER CODE BEGIN SPI1_MspInit 0 */

  /* USER CODE END SPI1_MspInit 0 */
    /* SPI1 clock enable */
    __HAL_RCC_SPI1_CLK_ENABLE();

    __HAL_RCC_GPIOA_CLK_ENABLE();
    /**SPI1 GPIO Configuration
    PA5     ------> SPI1_SCK
    PA6     ------> SPI1_MISO
    PA7     ------> SPI1_MOSI
    */
    GPIO_InitStruct.Pin = HALL_SPI_SCK_Pin|HALL_SPI_MISO_Pin|HALL_SPI_MOSI_Pin;
    GPIO_InitStruct.Mode = GPIO_MODE_AF_PP;
    GPIO_InitStruct.Pull = GPIO_NOPULL;
    GPIO_InitStruct.Speed = GPIO_SPEED_FREQ_LOW;
    GPIO_InitStruct.Alternate = GPIO_AF5_SPI1;
    HAL_GPIO_Init(GPIOA, &GPIO_InitStruct);

    /* SPI1 interrupt Init */
    HAL_NVIC_SetPriority(SPI1_IRQn, 0, 0);
    HAL_NVIC_EnableIRQ(SPI1_IRQn);
  /* USER CODE BEGIN SPI1_MspInit 1 */

  /* USER CODE END SPI1_MspInit 1 */
  }
}

void HAL_SPI_MspDeInit(SPI_HandleTypeDef* spiHandle)
{

  if(spiHandle->Instance==SPI1)
  {
  /* USER CODE BEGIN SPI1_MspDeInit 0 */

  /* USER CODE END SPI1_MspDeInit 0 */
    /* Peripheral clock disable */
    __HAL_RCC_SPI1_CLK_DISABLE();

    /**SPI1 GPIO Configuration
    PA5     ------> SPI1_SCK
    PA6     ------> SPI1_MISO
    PA7     ------> SPI1_MOSI
    */
    HAL_GPIO_DeInit(GPIOA, HALL_SPI_SCK_Pin|HALL_SPI_MISO_Pin|HALL_SPI_MOSI_Pin);

    /* SPI1 interrupt Deinit */
    HAL_NVIC_DisableIRQ(SPI1_IRQn);
  /* USER CODE BEGIN SPI1_MspDeInit 1 */

  /* USER CODE END SPI1_MspDeInit 1 */
  }
}

/* USER CODE BEGIN 1 */

/* USER CODE END 1 */

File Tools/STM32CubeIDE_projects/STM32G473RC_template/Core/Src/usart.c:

/* USER CODE BEGIN Header */
/**
  ******************************************************************************
  * @file    usart.c
  * @brief   This file provides code for the configuration
  *          of the USART instances.
  ******************************************************************************
  * @attention
  *
  * Copyright (c) 2025 STMicroelectronics.
  * All rights reserved.
  *
  * This software is licensed under terms that can be found in the LICENSE file
  * in the root directory of this software component.
  * If no LICENSE file comes with this software, it is provided AS-IS.
  *
  ******************************************************************************
  */
/* USER CODE END Header */
/* Includes ------------------------------------------------------------------*/
#include "usart.h"

/* USER CODE BEGIN 0 */

/* USER CODE END 0 */

UART_HandleTypeDef huart1;

/* USART1 init function */

void MX_USART1_UART_Init(void)
{

  /* USER CODE BEGIN USART1_Init 0 */

  /* USER CODE END USART1_Init 0 */

  /* USER CODE BEGIN USART1_Init 1 */

  /* USER CODE END USART1_Init 1 */
  huart1.Instance = USART1;
  huart1.Init.BaudRate = 460800;
  huart1.Init.WordLength = UART_WORDLENGTH_8B;
  huart1.Init.StopBits = UART_STOPBITS_1;
  huart1.Init.Parity = UART_PARITY_NONE;
  huart1.Init.Mode = UART_MODE_TX_RX;
  huart1.Init.HwFlowCtl = UART_HWCONTROL_NONE;
  huart1.Init.OverSampling = UART_OVERSAMPLING_16;
  huart1.Init.OneBitSampling = UART_ONE_BIT_SAMPLE_DISABLE;
  huart1.Init.ClockPrescaler = UART_PRESCALER_DIV1;
  huart1.AdvancedInit.AdvFeatureInit = UART_ADVFEATURE_NO_INIT;
  if (HAL_UART_Init(&huart1) != HAL_OK)
  {
    Error_Handler();
  }
  if (HAL_UARTEx_SetTxFifoThreshold(&huart1, UART_TXFIFO_THRESHOLD_1_8) != HAL_OK)
  {
    Error_Handler();
  }
  if (HAL_UARTEx_SetRxFifoThreshold(&huart1, UART_RXFIFO_THRESHOLD_1_8) != HAL_OK)
  {
    Error_Handler();
  }
  if (HAL_UARTEx_DisableFifoMode(&huart1) != HAL_OK)
  {
    Error_Handler();
  }
  /* USER CODE BEGIN USART1_Init 2 */

  /* USER CODE END USART1_Init 2 */

}

void HAL_UART_MspInit(UART_HandleTypeDef* uartHandle)
{

  GPIO_InitTypeDef GPIO_InitStruct = {0};
  RCC_PeriphCLKInitTypeDef PeriphClkInit = {0};
  if(uartHandle->Instance==USART1)
  {
  /* USER CODE BEGIN USART1_MspInit 0 */

  /* USER CODE END USART1_MspInit 0 */

  /** Initializes the peripherals clocks
  */
    PeriphClkInit.PeriphClockSelection = RCC_PERIPHCLK_USART1;
    PeriphClkInit.Usart1ClockSelection = RCC_USART1CLKSOURCE_PCLK2;
    if (HAL_RCCEx_PeriphCLKConfig(&PeriphClkInit) != HAL_OK)
    {
      Error_Handler();
    }

    /* USART1 clock enable */
    __HAL_RCC_USART1_CLK_ENABLE();

    __HAL_RCC_GPIOB_CLK_ENABLE();
    /**USART1 GPIO Configuration
    PB6     ------> USART1_TX
    PB7     ------> USART1_RX
    */
    GPIO_InitStruct.Pin = UART_TX_Pin|UART_RX_Pin;
    GPIO_InitStruct.Mode = GPIO_MODE_AF_PP;
    GPIO_InitStruct.Pull = GPIO_NOPULL;
    GPIO_InitStruct.Speed = GPIO_SPEED_FREQ_LOW;
    GPIO_InitStruct.Alternate = GPIO_AF7_USART1;
    HAL_GPIO_Init(GPIOB, &GPIO_InitStruct);

  /* USER CODE BEGIN USART1_MspInit 1 */

  /* USER CODE END USART1_MspInit 1 */
  }
}

void HAL_UART_MspDeInit(UART_HandleTypeDef* uartHandle)
{

  if(uartHandle->Instance==USART1)
  {
  /* USER CODE BEGIN USART1_MspDeInit 0 */

  /* USER CODE END USART1_MspDeInit 0 */
    /* Peripheral clock disable */
    __HAL_RCC_USART1_CLK_DISABLE();

    /**USART1 GPIO Configuration
    PB6     ------> USART1_TX
    PB7     ------> USART1_RX
    */
    HAL_GPIO_DeInit(GPIOB, UART_TX_Pin|UART_RX_Pin);

  /* USER CODE BEGIN USART1_MspDeInit 1 */

  /* USER CODE END USART1_MspDeInit 1 */
  }
}

/* USER CODE BEGIN 1 */

/* USER CODE END 1 */

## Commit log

2025-03-31 pcb: Add BOM
2025-04-02 pcb: Add electrical schematic
2025-04-02 project: Update README.md
2025-04-13 pcb: Add layout & gerbers
2025-04-13 project: Create README.md
2025-04-26 enclosure: Add enclosure STL files
2025-04-27 pcb: Update BOM
2025-04-27 pcb: Add PCB step files
2025-04-27 project: Add datasheets
2025-04-27 project: Add gitignore file
2025-04-27 cube: Add Stm32CubeIde project template
2025-04-27 cube: Create README.md for STM32CubeIde project template
2025-04-29 setup: Add project skeleton
2025-04-29 setup: Add build and debug configuration
